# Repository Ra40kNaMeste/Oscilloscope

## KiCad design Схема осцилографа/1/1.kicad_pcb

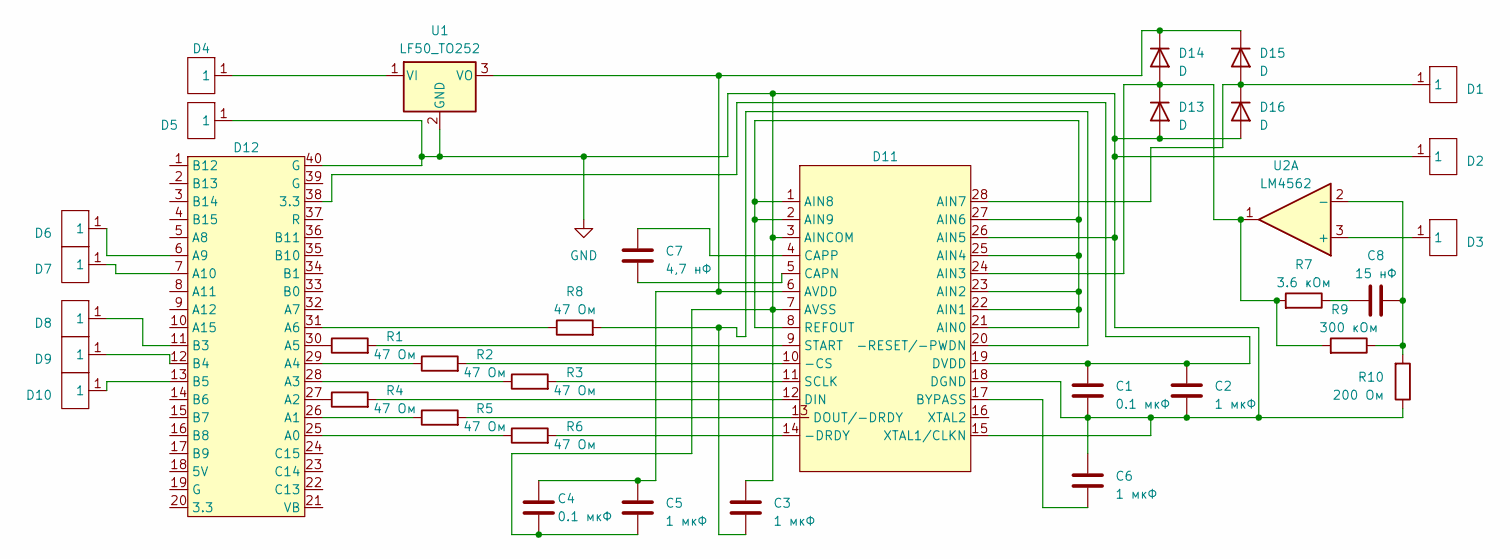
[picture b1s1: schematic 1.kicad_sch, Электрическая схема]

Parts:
C1, C4: 0.1 мкФ; C_0805_2012Metric_Pad1.18x1.45mm_HandSolder
C2, C5, C6: 1 мкФ; CP_Radial_D4.0mm_P2.00mm
C3: 1 мкФ; CP_Radial_D8.0mm_P3.50mm
C7: 4,7 нФ; C_0504_1310Metric_Pad0.83x1.28mm_HandSolder
C8: 15 нФ; C_0805_2012Metric_Pad1.18x1.45mm_HandSolder
D1, D2, D3, D4, D5, D6, D7, D8, D9, D10: simply
D11: ADC126xBase
D12: stm32f103xx
D13, D14, D15, D16: D; D_5KPW_P7.62mm_Vertical_AnodeUp
R1, R2, R3, R4, R5, R6, R8: 47 Ом; R_Box_L13.0mm_W4.0mm_P9.00mm
R7: 3.6 кОм; R_Box_L13.0mm_W4.0mm_P9.00mm
R9: 300 кОм; R_Box_L13.0mm_W4.0mm_P9.00mm
R10: 200 Ом; R_Box_L13.0mm_W4.0mm_P9.00mm
U1: LF50_TO252; TO-252-2
U2: LM4562; DIP-8_W6.35mm

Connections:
GND: C1.2, C2.2, C3.1, C4.2, C5.2, C6.1, D2.1, D5.1, D11.3 (AINCOM), D11.7 (AVSS), D11.15 (XTAL1/CLKN), D11.18 (DGND), D11.26 (AIN5), D12.40 (G), D13.2 (A), D16.2 (A), R10.1, U1.2 (GND)
unnamed: C8.2, R7.1
unnamed: D11.10 (-CS), R2.2
unnamed: D11.14 (-DRDY), R6.2
unnamed: C3.2, D11.20 (-RESET/-PWDN), R8.2
unnamed: D11.1 (AIN8), D11.2 (AIN9), D11.8 (REFOUT), D11.21 (AIN0), D11.22 (AIN1), D11.23 (AIN2), D11.25 (AIN4), D11.27 (AIN6)
unnamed: D11.24 (AIN3), D13.1 (K), D14.2 (A), R7.2, R9.2, U2.1
unnamed: D1.1, D11.28 (AIN7), D15.2 (A), D16.1 (K)
unnamed: C4.1, C5.1, D11.6 (AVDD), D14.1 (K), D15.1 (K), U1.3 (VO)
unnamed: C6.2, D11.17 (BYPASS)
unnamed: C7.2, D11.5 (CAPN)
unnamed: C7.1, D11.4 (CAPP)
unnamed: D11.12 (DIN), R4.2
unnamed: D11.13 (DOUT/-DRDY), R5.2
unnamed: C1.1, C2.1, D11.19 (DVDD), D12.38 (3.3)
unnamed: D11.11 (SCLK), R3.2
unnamed: D11.9 (START), R1.2
unnamed: D12.25 (A0), R6.1
unnamed: D12.26 (A1), R5.1
unnamed: D12.27 (A2), R4.1
unnamed: D12.28 (A3), R3.1
unnamed: D12.29 (A4), R2.1
unnamed: D12.30 (A5), R1.1
unnamed: D12.31 (A6), R8.1
unnamed: D6.1, D12.6 (A9)
unnamed: D7.1, D12.7 (A10)
unnamed: D8.1, D12.11 (B3)
unnamed: D9.1, D12.12 (B4)
unnamed: D10.1, D12.13 (B5)
unnamed: D4.1, U1.1 (VI)
unnamed: D3.1, U2.3 (+)
unnamed: C8.1, R9.1, R10.2, U2.2 (-)

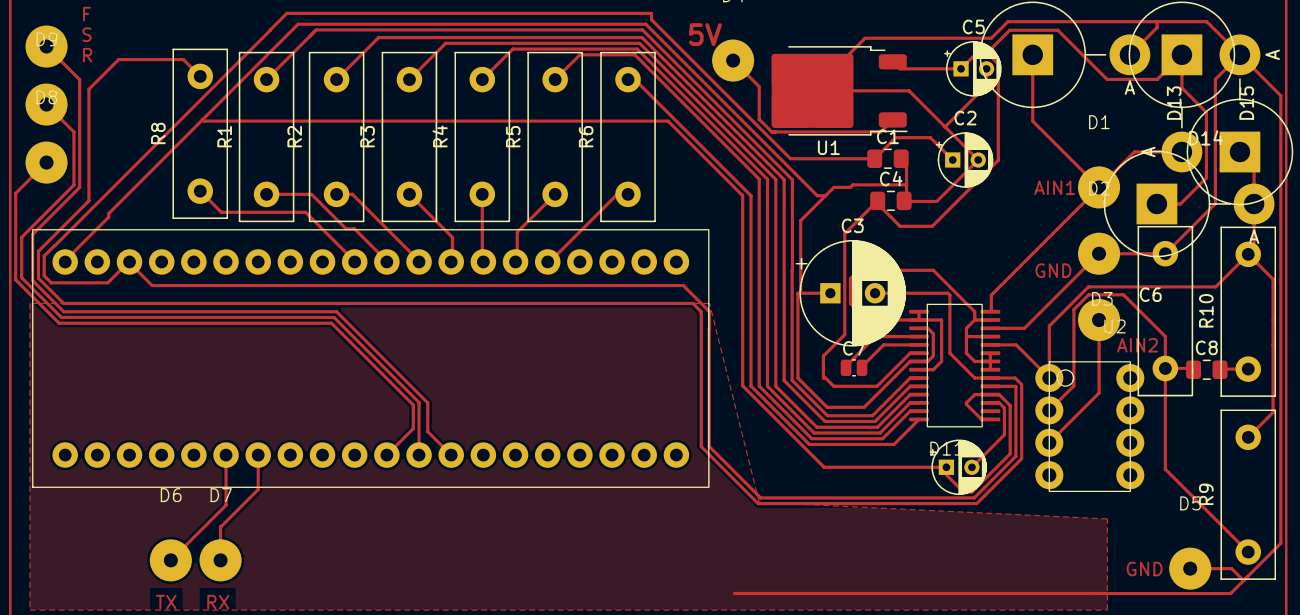
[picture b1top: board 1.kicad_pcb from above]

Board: 2 copper layers, 36 parts (0 on the bottom side), 32 nets.

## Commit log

2023-04-05 fixed bugs microcontroller
2023-04-05 Add Desktop app and gitignore
2023-04-06 Add port user setting
2023-04-12 Add run only monochrome command
2023-04-13 Add RunMonochrome command
2023-04-13 Adding support old ADC
2023-04-14 Fix bugs
2023-04-14 Add rewindMonochrome command and fix bugs
2023-04-14 Change firmware STM controller. STM Time convert STM regulated by PC
2023-04-21 Add asynchrone doblicade operation
2023-04-21 Refactoring viewmodel: append attribute for update condition changed command
2023-04-23 Fix async commands
2023-04-23 Refactoring logic microcontroller
2023-04-23 Refactoring VS code by new rules for tranfer command to STM
2023-04-23 Change gitignore, add russian resources, change program window name
2023-04-26 Refactoring ViewModel amd ADCLibrary. Add Calibration time in ADC ohne start or stop monochrome
2023-04-27 Add run and rewind command by timer inside
2023-07-19 Промежуточный коммит
